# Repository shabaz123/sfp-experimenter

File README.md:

# sfp-experimenter
A KiCad v8 version of the 'sfp-experimenter' board at https://gitea.osmocom.org/electronics/osmo-small-hardware/src/branch/master/sfp-breakout

License: Same as the original source at https://gitea.osmocom.org/electronics/osmo-small-hardware/src/branch/master/sfp-breakout i.e. CC-BY-SA

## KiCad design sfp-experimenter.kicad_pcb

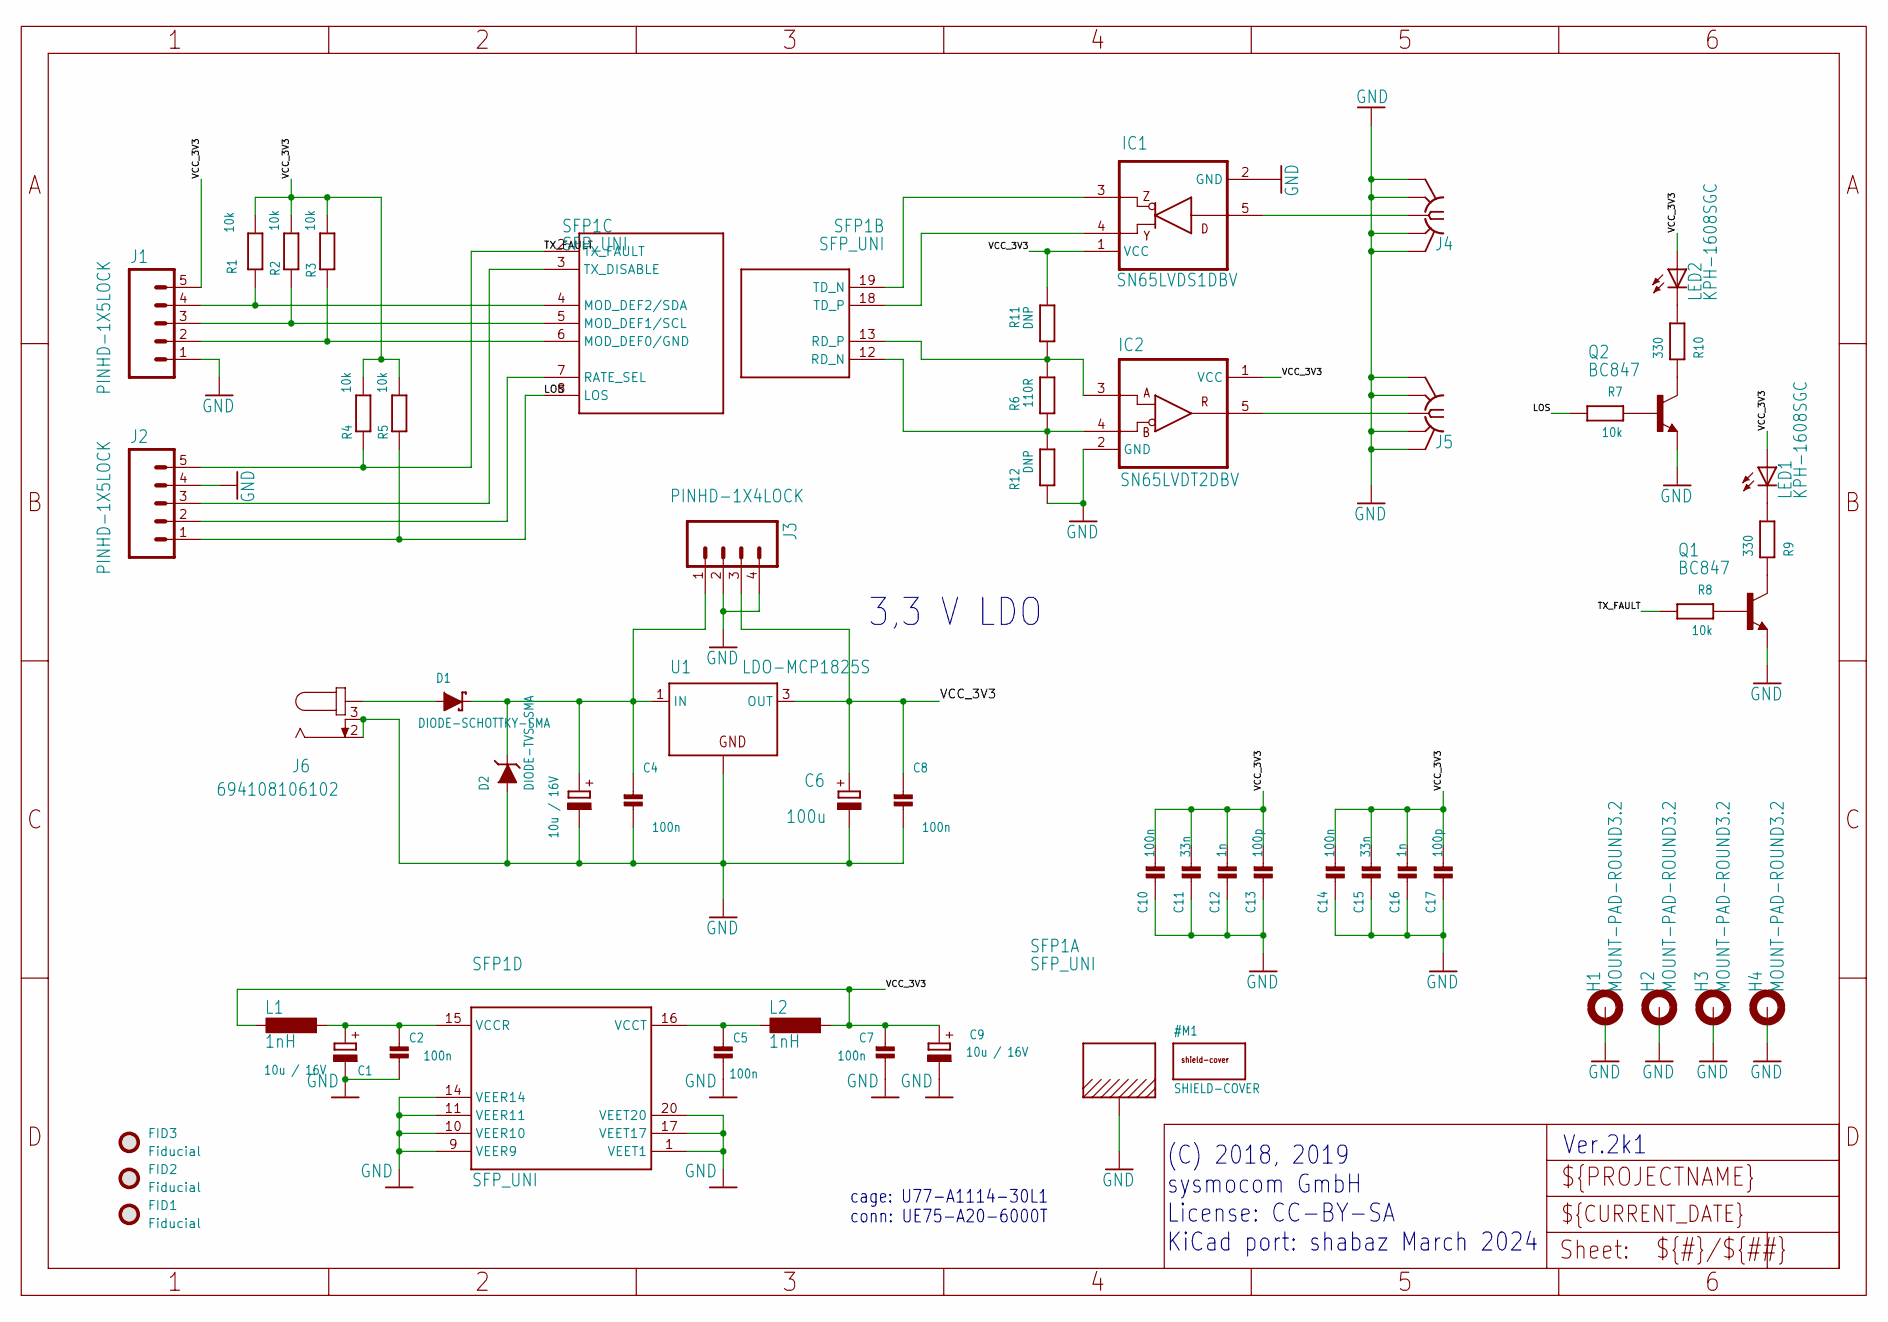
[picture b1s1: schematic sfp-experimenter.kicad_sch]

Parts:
C1, C3, C9: 10u / 16V; CPOL1206; MANUFACTURERPARTNUMBER CL31A106KOHNNNE
C2, C4, C5, C7, C8, C10, C14: 100n; _0603; MANUFACTURERPARTNUMBER CL10B104KO8NNNC
C6: 100u; CT6032; MANUFACTURERPARTNUMBER T520C107M006ATE045
C11, C15: 33n; _0603; MANUFACTURERPARTNUMBER 06035C333JAT2A
C12, C16: 1n; _0603; MANUFACTURERPARTNUMBER CC0603KRX7R9BB102
C13, C17: 100p; _0603; MANUFACTURERPARTNUMBER CC0603JRNPO9BN101
D1: DIODE-SCHOTTKY-SMA; SMADIODE; MANUFACTURERPARTNUMBER STPS2L60A
D2: DIODE-TVS-SMA; SMADIODE; MANUFACTURERPARTNUMBER SMAJ5.0A
FID1, FID2, FID3: Fiducial; Fiducial_1mm_Mask3mm
H1, H2, H3, H4: MOUNT-PAD-ROUND3.2; 3,2-PAD; MANUFACTURERPARTNUMBER UNKNOWN MANUFACTURER PART NUMBER
IC1: SN65LVDS1DBV; SOT23-5; MANUFACTURERPARTNUMBER SN65LVDS1DBVR
IC2: SN65LVDT2DBV; SOT23-5; MANUFACTURERPARTNUMBER PI90LV02TEX
J1, J2: PINHD-1X5LOCK; 1X05_LOCK; MANUFACTURERPARTNUMBER UNKNOWN MANUFACTURER PART NUMBER
J3: PINHD-1X4LOCK; 1X04_LOCK; MANUFACTURERPARTNUMBER UNKNOWN MANUFACTURER PART NUMBER
J4, J5: SMA-F-S-EDGE; MANUFACTURERPARTNUMBER UNKNOWN MANUFACTURER PART NUMBER
J6: 694108106102; MANUFACTURERPARTNUMBER PJ-002BH-SMT-TR
L1, L2: 1nH; 0603; MANUFACTURERPARTNUMBER AIMC-0603-1N0S-T
LED1, LED2: KPH-1608SGC; CHIP-LED0603; MANUFACTURERPARTNUMBER UNKNOWN MANUFACTURER PART NUMBER
Q1, Q2: BC847; SOT23-BEC; MANUFACTURERPARTNUMBER BC847C,215
R1, R2, R3, R4, R5, R7, R8: 10k; _0603; MANUFACTURERPARTNUMBER RC0603FR-0710KL
R6: 110R; _0402; MANUFACTURERPARTNUMBER RC0603FR-13110RL
R9, R10: 330; _0603; MANUFACTURERPARTNUMBER ERJ-3GEYJ331V
R11: DNP; _0603; MANUFACTURERPARTNUMBER UNKNOWN MANUFACTURER PART NUMBER
R12: DNP; _0603; MANUFACTURERPARTNUMBER RK73H1JTTD1003F
SFP1: SFP_UNI; SFP_COMBINED; MANUFACTURERPARTNUMBER UE75-A20-6000T
U1: LDO-MCP1825S; SOT223; MANUFACTURERPARTNUMBER MCP1825ST-3302E/DB

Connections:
/LOS: J2.1, R5.1, R7.2, SFP1.8 (LOS)
/TX_FAULT: J2.5, R4.1, R8.2, SFP1.2 (TX_FAULT)
/VCC_3V3: C6.+, C7.1, C8.1, C9.+, C10.1, C11.1, C12.1, C13.1, C14.1, C15.1, C16.1, C17.1, IC1.1 (VCC), IC2.1 (VCC), J1.5, J3.3, L1.2, L2.1, LED1.A, LED2.A, R1.2, R2.2, R3.2, R4.2, R5.2, R11.1, U1.3 (OUT)
GND: C1.-, C2.2, C3.-, C4.2, C5.2, C6.-, C7.2, C8.2, C9.-, C10.2, C11.2, C12.2, C13.2, C14.2, C15.2, C16.2, C17.2, D2.A, H1.B3,2 (MOUNT), H2.B3,2 (MOUNT), H3.B3,2 (MOUNT), H4.B3,2 (MOUNT), IC1.2 (GND), IC2.2 (GND), J1.1, J2.4, J3.2, J3.4, J4.BG1 (GND@1), J4.BG2 (GND@4), J4.TG1 (GND@2), J4.TG2 (GND@3), J5.BG1 (GND@1), J5.BG2 (GND@4), J5.TG1 (GND@2), J5.TG2 (GND@3), J6.2, J6.3, Q1.E, Q2.E, R12.2, SFP1.1 (VEET1), SFP1.9 (VEER9), SFP1.10 (VEER10), SFP1.11 (VEER11), SFP1.14 (VEER14), SFP1.17 (VEET17), SFP1.20 (VEET20), SFP1.A1 (CAGE), SFP1.A2 (CAGE), SFP1.A3 (CAGE), SFP1.A4 (CAGE), SFP1.A5 (CAGE), SFP1.A6 (CAGE), SFP1.A7 (CAGE), SFP1.A8 (CAGE), SFP1.A10 (CAGE), SFP1.A11 (CAGE), SFP1.A12 (CAGE), SFP1.B1 (CAGE), SFP1.B2 (CAGE), SFP1.B3 (CAGE), SFP1.B4 (CAGE), SFP1.B5 (CAGE), SFP1.B6 (CAGE), SFP1.B7 (CAGE), SFP1.B8 (CAGE), SFP1.B10 (CAGE), U1.2 (GND), U1.4 (GND)
unnamed: D1.A, J6.1, J6.1-1 (1)
unnamed: IC1.5 (D), J4.C (1)
unnamed: IC1.4 (Y), SFP1.18 (TD_P)
unnamed: IC1.3 (Z), SFP1.19 (TD_N)
unnamed: IC2.3 (A), R6.1, R11.2, SFP1.13 (RD_P)
unnamed: IC2.4 (B), R6.2, R12.1, SFP1.12 (RD_N)
unnamed: IC2.5 (R), J5.C (1)
unnamed: LED1.C, R9.2
unnamed: LED2.C, R10.2
unnamed: Q1.B, R8.1
unnamed: Q1.C, R9.1
unnamed: Q2.B, R7.1
unnamed: Q2.C, R10.1
unnamed: J1.2, R3.1, SFP1.6 (MOD_DEF0/GND)
unnamed: J1.3, R2.1, SFP1.5 (MOD_DEF1/SCL)
unnamed: J1.4, R1.1, SFP1.4 (MOD_DEF2/SDA)
unnamed: J2.2, SFP1.7 (RATE_SEL)
unnamed: J2.3, SFP1.3 (TX_DISABLE)
unnamed: C1.+, C2.1, L1.1, SFP1.15 (VCCR)
unnamed: C5.1, L2.2, SFP1.16 (VCCT)
unnamed: C3.+, C4.1, D1.C, D2.C, J3.1, U1.1 (IN)

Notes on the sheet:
conn: UE75-A20-6000T
cage: U77-A1114-30L1
3,3 V LDO
Ver.2k1
(C) 2018, 2019 sysmocom GmbH License: CC-BY-SA KiCad port: shabaz March 2024

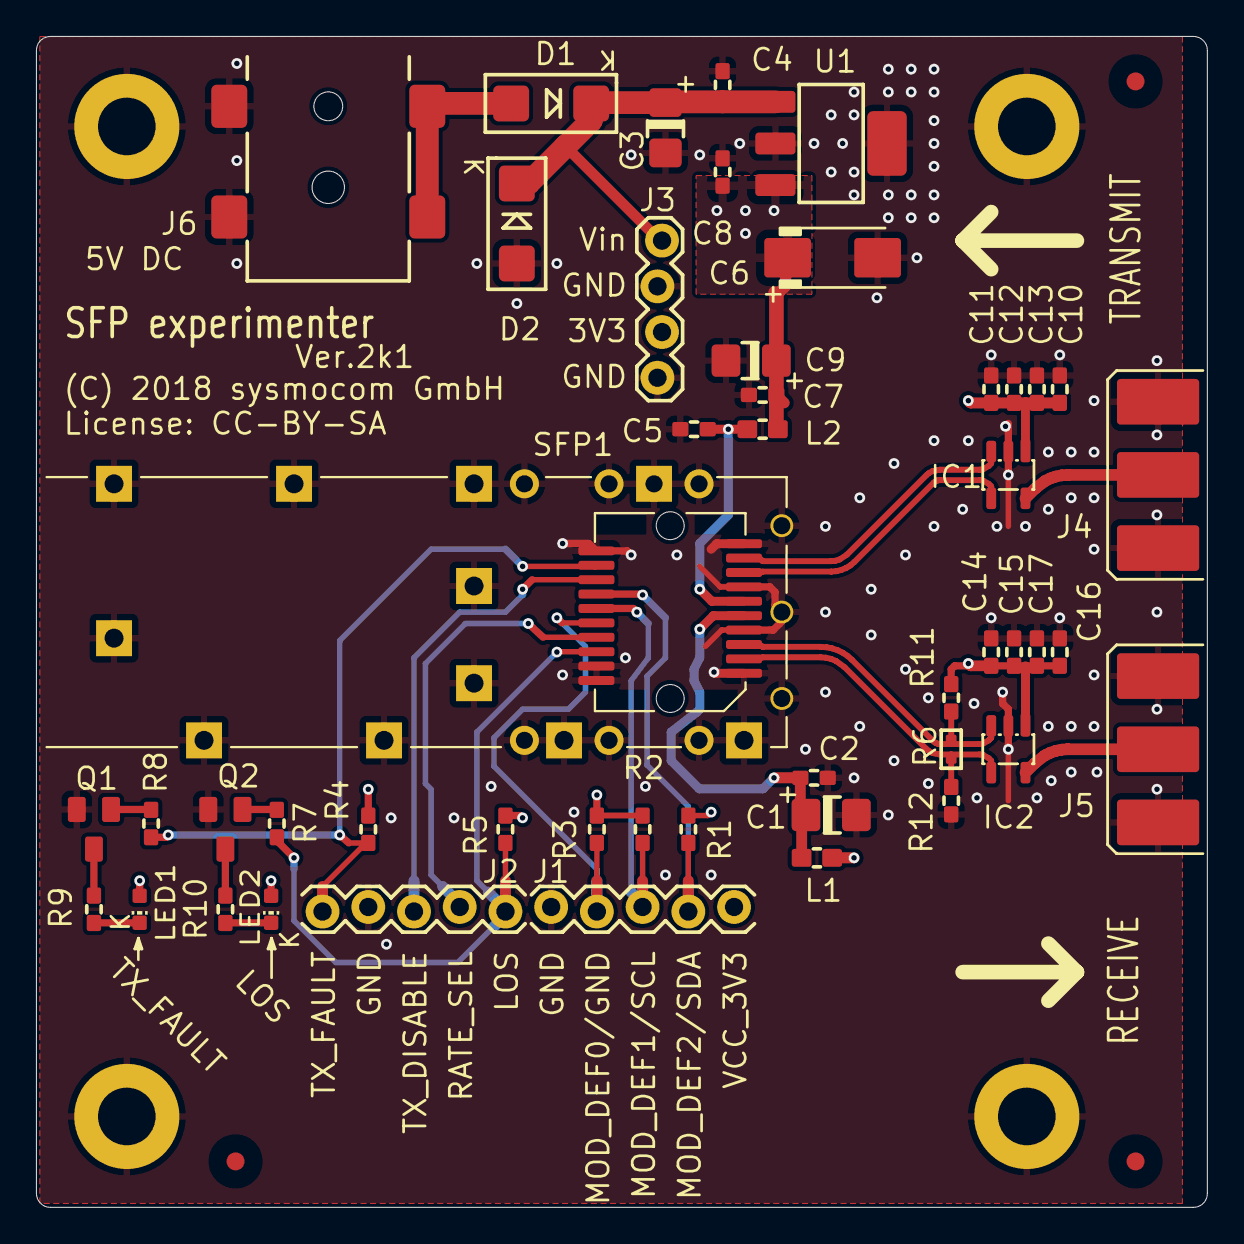
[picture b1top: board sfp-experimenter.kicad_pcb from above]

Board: 4 copper layers, 65.1 x 65.1 mm, 54 parts (0 on the bottom side), 25 nets.

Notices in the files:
sfp-experimenter.kicad_pcb:
(C) 2018 sysmocom GmbH
License: CC-BY-SA
